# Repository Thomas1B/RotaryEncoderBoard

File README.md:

# Rotary Encoder Board

This a printed circuit board (PCB) designed to make a rotary encoder easier to prototype.

This was created using KiCad. To open the KiCad file, double click the ".pro" file.

See https://github.com/Thomas1B/Arduino-Stuff/tree/main/Rotary_Encoder_tester for Arduino Code.

## Circuit Diagram

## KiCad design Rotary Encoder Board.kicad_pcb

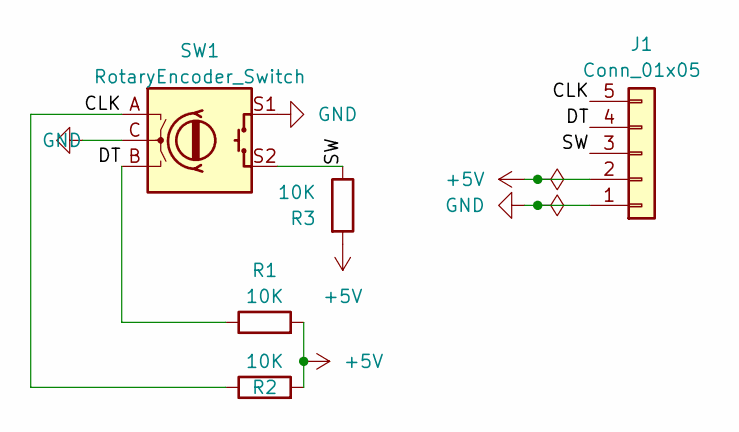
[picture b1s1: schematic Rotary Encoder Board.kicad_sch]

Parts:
J1: Conn_01x05; PinHeader_1x05_P2.54mm_Vertical
R1, R2, R3: 10K; R_0805_2012Metric_Pad1.20x1.40mm_HandSolder
SW1: RotaryEncoder_Switch; Rotary Encoder

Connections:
+5V: J1.2, R1.2, R2.2, R3.2
/CLK: J1.5, R2.1, SW1.A
/DT: J1.4, R1.1, SW1.B
/SW: J1.3, R3.1, SW1.S2
GND: J1.1, SW1.C, SW1.MP, SW1.S1

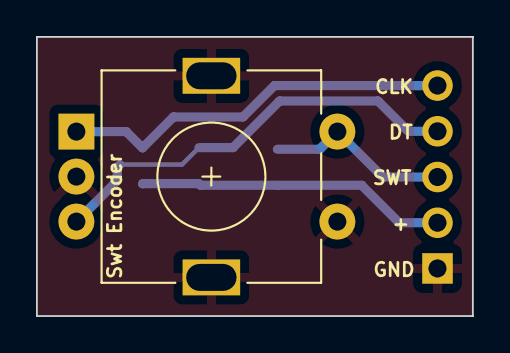
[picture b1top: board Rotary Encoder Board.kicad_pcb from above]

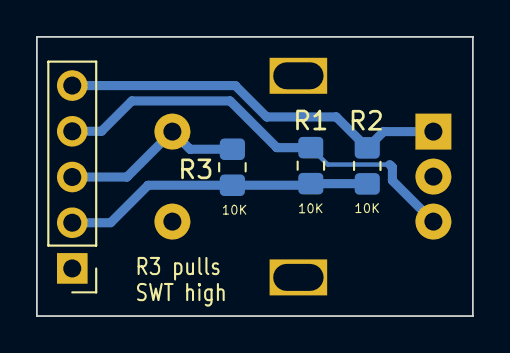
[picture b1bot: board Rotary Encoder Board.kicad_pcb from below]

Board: 2 copper layers, 24.2 x 15.5 mm, 5 parts (4 on the bottom side), 5 nets.

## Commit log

2023-07-28 Create LICENSE
2023-07-28 added KiCad Files
2023-07-28 updated KiCad Model
2023-09-28 sync everything
